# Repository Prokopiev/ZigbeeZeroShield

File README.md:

# ZigbeeZeroShield

## About ZigbeeZeroShield

ZigbeeZeroShield is a simple Raspberry Pi Zero W shield. It provides zigbee functionality and can work as generic router to form zigbee network. It uses E18-MS1PA1-PCB for communication.
Works well with [zigbee2mqtt.io](https://www.zigbee2mqtt.io/)

[E18-MS1PA1-PCB Overview](http://www.ebyte.com/en/product-view-news.aspx?id=121)

## License

The ZigbeeZeroShield is open-source software licensed under the [MIT license](https://opensource.org/licenses/MIT).

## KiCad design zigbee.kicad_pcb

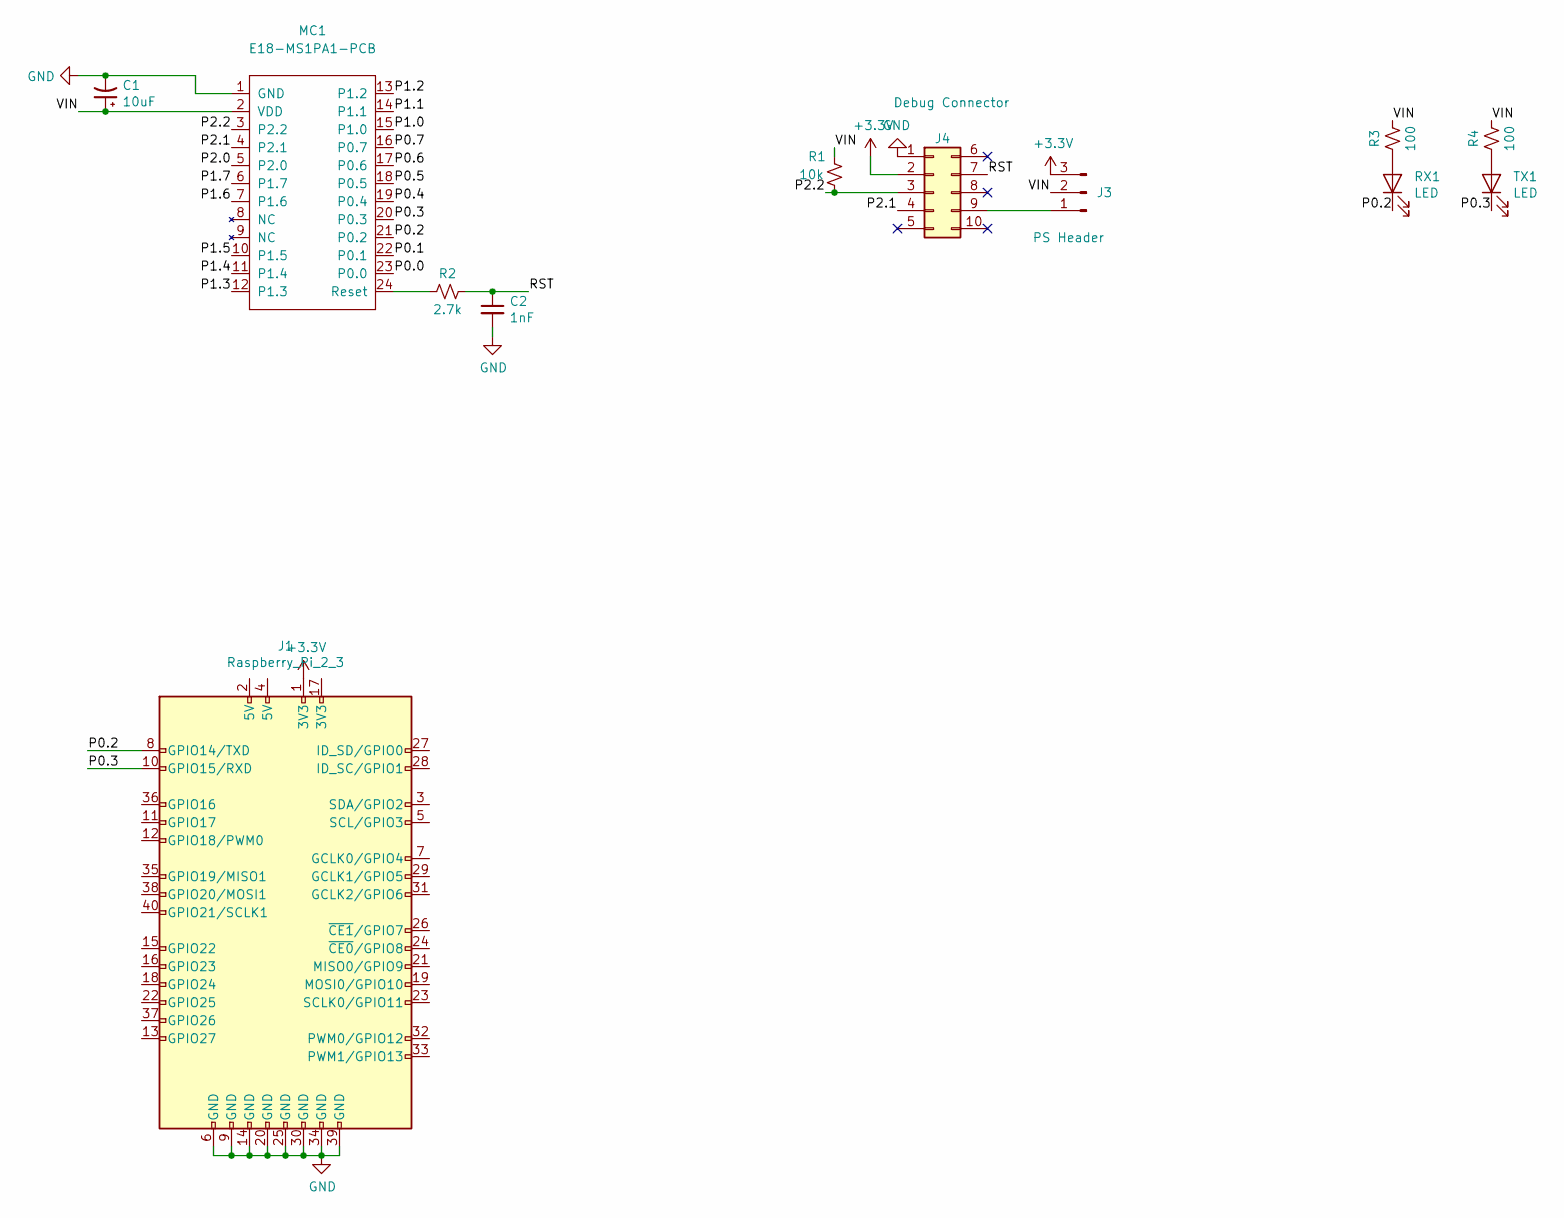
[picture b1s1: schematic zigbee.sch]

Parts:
C1: 10uF; CP_EIA-3528-21_Kemet-B
C2: 1nF; C_0603_1608Metric
J1: Raspberry_Pi_2_3; PinHeader_2x20_P2.54mm_Vertical
J3: PS Header; PinHeader_1x03_P2.54mm_Vertical
J4: Debug Connector; PinHeader_2x05_P2.54mm_Vertical
MC1: E18-MS1PA1-PCB
R1: 10k; R_0603_1608Metric
R2: 2.7k; R_0603_1608Metric
R3, R4: 100; R_0603_1608Metric
RX1: LED; LED_0603_1608Metric
TX1: LED; LED_0603_1608Metric

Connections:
+3V3: J1.1 (3V3), J3.3, J4.2
/P0.0: MC1.23 (P0.0)
/P0.1: MC1.22 (P0.1)
/P0.2: J1.8 (GPIO14/TXD), MC1.21 (P0.2), RX1.1 (K)
/P0.3: J1.10 (GPIO15/RXD), MC1.20 (P0.3), TX1.1 (K)
/P0.4: MC1.19 (P0.4)
/P0.5: MC1.18 (P0.5)
/P0.6: MC1.17 (P0.6)
/P0.7: MC1.16 (P0.7)
/P1.0: MC1.15 (P1.0)
/P1.1: MC1.14 (P1.1)
/P1.2: MC1.13 (P1.2)
/P1.3: MC1.12 (P1.3)
/P1.4: MC1.11 (P1.4)
/P1.5: MC1.10 (P1.5)
/P1.6: MC1.7 (P1.6)
/P1.7: MC1.6 (P1.7)
/P2.0: MC1.5 (P2.0)
/P2.1: J4.4, MC1.4 (P2.1)
/P2.2: J4.3, MC1.3 (P2.2), R1.2
/RST: C2.1, J4.7, R2.2
/VIN: C1.1, J3.2, MC1.2 (VDD), R1.1, R3.2, R4.2
GND: C1.2, C2.2, J1.6 (GND), J1.9 (GND), J1.14 (GND), J1.20 (GND), J1.25 (GND), J1.30 (GND), J1.34 (GND), J1.39 (GND), J4.1, MC1.1 (GND)
unnamed: J3.1, J4.9
unnamed: MC1.24 (Reset), R2.1
unnamed: R3.1, RX1.2 (A)
unnamed: R4.1, TX1.2 (A)

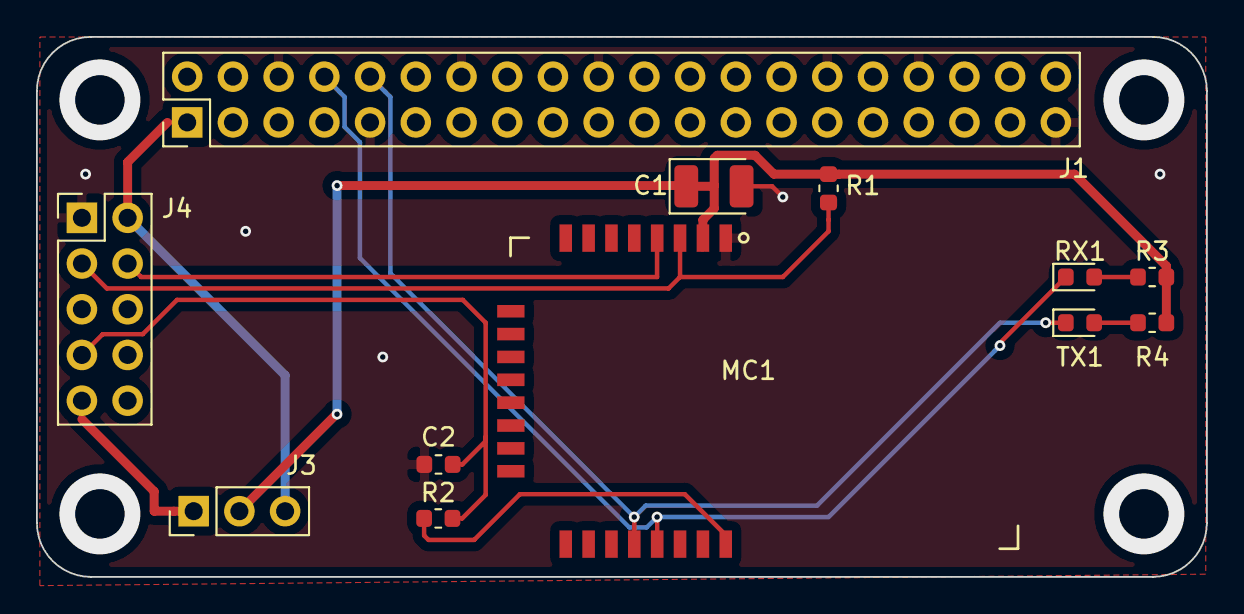
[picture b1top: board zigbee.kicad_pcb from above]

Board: 2 copper layers, 65.0 x 30.0 mm, 12 parts (0 on the bottom side), 12 nets.

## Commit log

2019-10-17 init

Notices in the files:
README.md:
License: MIT
